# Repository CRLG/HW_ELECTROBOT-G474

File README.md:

# HW_ELECTROBOT-G474
Carte fillepour Nucleo64 G474RE

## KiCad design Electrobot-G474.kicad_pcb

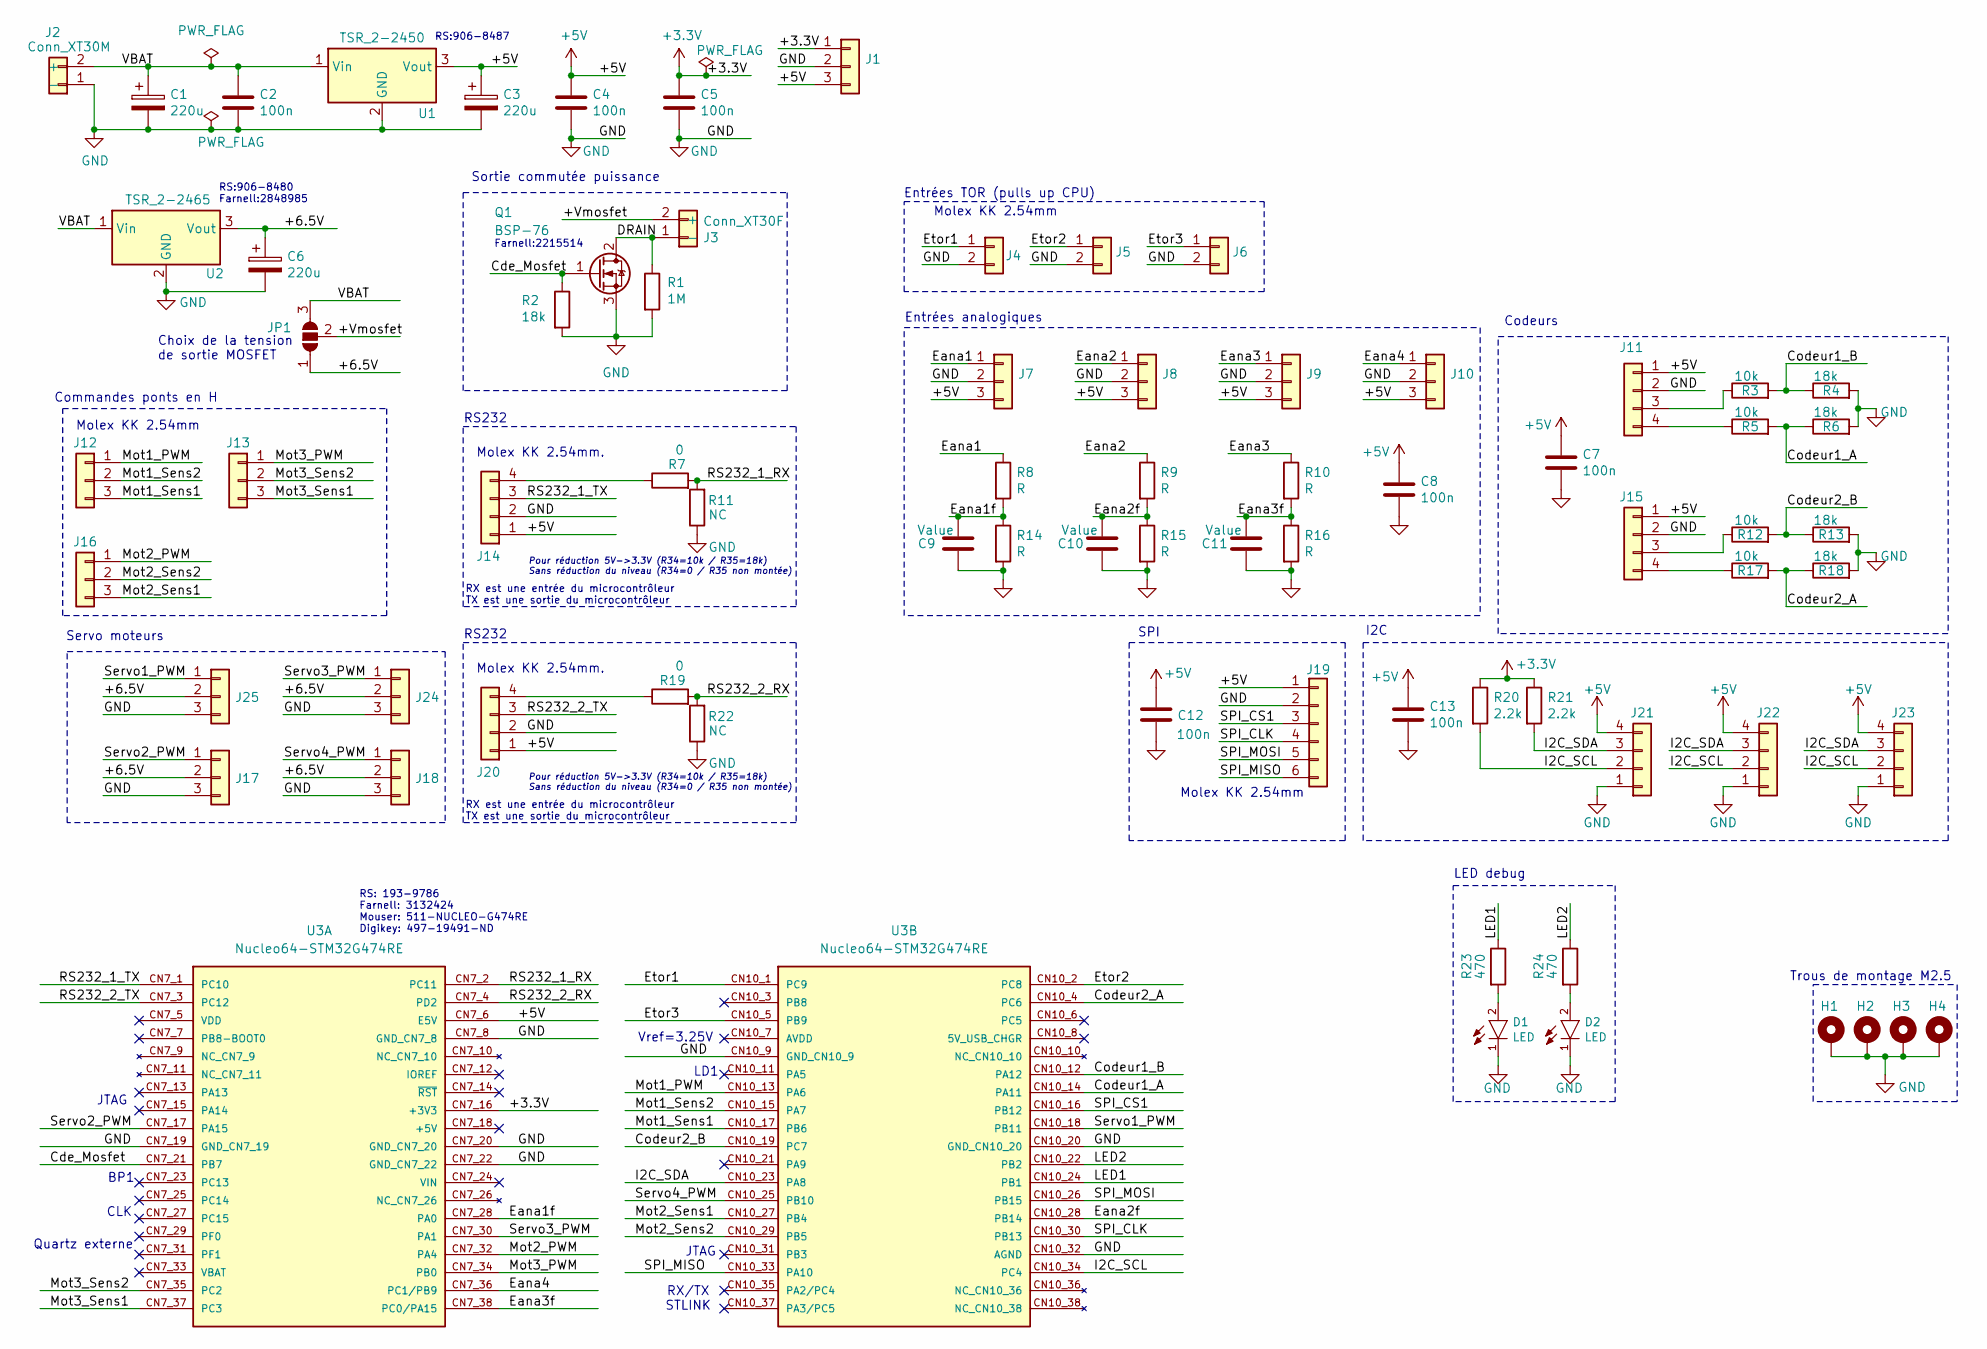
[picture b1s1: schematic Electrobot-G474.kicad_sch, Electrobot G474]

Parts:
C1, C3, C6: 220u; C_Radial_D8.0mm_H11.5mm_P3.50mm
C2, C4, C5, C7, C8, C12, C13: 100n; C_1206_3216Metric
C9, C10, C11: Value; C_1206_3216Metric
D1, D2: LED; LED_1206_3216Metric
H1, H2, H3, H4: MountingHole_Pad; MountingHole_2.7mm_M2.5_Pad
J1, J7, J8, J9, J10: Conn_01x03; Molex_KK-254_AE-6410-03A_1x03_P2.54mm_Vertical
J2: Conn_XT30M; AMASS_XT30UPB-M_1x02_P5.0mm_Vertical
J3: Conn_XT30F; AMASS_XT30UPB-F_1x02_P5.0mm_Vertical
J4, J5, J6: Conn_01x02; Molex_KK-254_AE-6410-02A_1x02_P2.54mm_Vertical
J11, J14, J15, J20, J21, J22, J23: Conn_01x04; Molex_KK-254_AE-6410-04A_1x04_P2.54mm_Vertical
J12, J13, J16: Conn_01x04; Molex_KK-254_AE-6410-03A_1x03_P2.54mm_Vertical
J17, J18, J24, J25: Conn_01x03; Servomotor-3x254
J19: Conn_01x06; Molex_KK-254_AE-6410-06A_1x06_P2.54mm_Vertical
JP1: SolderJumper_3_Open; PinHeader_1x03_P2.54mm_Vertical
Q1: BSP-76; SOT-223-3_TabPin2
R1: 1M; R_1206_3216Metric
R2, R4, R6, R13, R18: 18k; R_1206_3216Metric
R3, R5, R12, R17: 10k; R_1206_3216Metric
R7, R19: 0; R_1206_3216Metric
R8, R9, R10, R14, R15, R16: R; R_1206_3216Metric
R11, R22: NC; R_1206_3216Metric
R20, R21: 2.2k; R_1206_3216Metric
R23, R24: 470; R_1206_3216Metric
U1: TSR_2-2450; Converter_DCDC_TRACO_TSR-2_THT
U2: TSR_2-2465; Converter_DCDC_TRACO_TSR-2_THT
U3: Nucleo64-STM32G474RE; Nucleo64-G474RE_ExtensionShield_Bottom

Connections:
+3.3V: C5.1, J1.1, R20.1, R21.1, U3.CN7_16 (+3V3)
+5V: C3.1, C4.1, C7.1, C8.1, C12.1, C13.1, J1.3, J7.3, J8.3, J9.3, J10.3, J11.1, J14.1, J15.1, J19.1, J20.1, J21.4, J22.4, J23.4, U1.3 (Vout), U3.CN7_6 (E5V)
/+6.5V: C6.1, J17.2, J18.2, J24.2, J25.2, JP1.1 (A), U2.3 (Vout)
/+Vmosfet: J3.2 (+), JP1.2 (C)
/Cde_Mosfet: Q1.1 (G), R2.1, U3.CN7_21 (PB7)
/Codeur1_A: R5.2, R6.1, U3.CN10_14 (PA11)
/Codeur1_B: R3.2, R4.1, U3.CN10_12 (PA12)
/Codeur2_A: R17.2, R18.1, U3.CN10_4 (PC6)
/Codeur2_B: R12.2, R13.1, U3.CN10_19 (PC7)
/DRAIN: J3.1 (-), Q1.2 (D), R1.1
/Eana1: J7.1, R8.1
/Eana1f: C9.2, R8.2, R14.1, U3.CN7_28 (PA0)
/Eana2: J8.1, R9.1
/Eana2f: C10.2, R9.2, R15.1, U3.CN10_28 (PB14)
/Eana3: J9.1, R10.1
/Eana3f: C11.2, R10.2, R16.1, U3.CN7_38 (PC0/PA15)
/Eana4: J10.1, U3.CN7_36 (PC1/PB9)
/Etor1: J4.1, U3.CN10_1 (PC9)
/Etor2: J5.1, U3.CN10_2 (PC8)
/Etor3: J6.1, U3.CN10_5 (PB9)
/I2C_SCL: J21.2, J22.2, J23.2, R20.2, U3.CN10_34 (PC4)
/I2C_SDA: J21.3, J22.3, J23.3, R21.2, U3.CN10_23 (PA8)
/LED1: R23.1, U3.CN10_24 (PB1)
/LED2: R24.1, U3.CN10_22 (PB2)
/Mot1_PWM: J12.1, U3.CN10_13 (PA6)
/Mot1_Sens1: J12.3, U3.CN10_17 (PB6)
/Mot1_Sens2: J12.2, U3.CN10_15 (PA7)
/Mot2_PWM: J16.1, U3.CN7_32 (PA4)
/Mot2_Sens1: J16.3, U3.CN10_27 (PB4)
/Mot2_Sens2: J16.2, U3.CN10_29 (PB5)
/Mot3_PWM: J13.1, U3.CN7_34 (PB0)
/Mot3_Sens1: J13.3, U3.CN7_37 (PC3)
/Mot3_Sens2: J13.2, U3.CN7_35 (PC2)
/RS232_1_RX: R7.2, R11.2, U3.CN7_2 (PC11)
/RS232_1_TX: J14.3, U3.CN7_1 (PC10)
/RS232_2_RX: R19.2, R22.2, U3.CN7_4 (PD2)
/RS232_2_TX: J20.3, U3.CN7_3 (PC12)
/SPI_CLK: J19.4, U3.CN10_30 (PB13)
/SPI_CS1: J19.3, U3.CN10_16 (PB12)
/SPI_MISO: J19.6, U3.CN10_33 (PA10)
/SPI_MOSI: J19.5, U3.CN10_26 (PB15)
/Servo1_PWM: J25.1, U3.CN10_18 (PB11)
/Servo2_PWM: J17.1, U3.CN7_17 (PA15)
/Servo3_PWM: J24.1, U3.CN7_30 (PA1)
/Servo4_PWM: J18.1, U3.CN10_25 (PB10)
/VBAT: C1.1, C2.1, J2.2 (+), JP1.3 (B), U1.1 (Vin), U2.1 (Vin)
GND: C1.2, C2.2, C3.2, C4.2, C5.2, C6.2, C7.2, C8.2, C9.1, C10.1, C11.1, C12.2, C13.2, D1.1 (C), D2.1 (C), H1.1, H2.1, H3.1, H4.1, J1.2, J2.1 (-), J4.2, J5.2, J6.2, J7.2, J8.2, J9.2, J10.2, J11.2, J14.2, J15.2, J17.3, J18.3, J19.2, J20.2, J21.1, J22.1, J23.1, J24.3, J25.3, Q1.3 (S), R1.2, R2.2, R4.2, R6.2, R11.1, R13.2, R14.2, R15.2, R16.2, R18.2, R22.1, U1.2 (GND), U2.2 (GND), U3.CN7_8 (GND_CN7_8), U3.CN7_19 (GND_CN7_19), U3.CN7_20 (GND_CN7_20), U3.CN7_22 (GND_CN7_22), U3.CN10_9 (GND_CN10_9), U3.CN10_20 (GND_CN10_20), U3.CN10_32 (AGND)
unnamed: D1.2 (A), R23.2
unnamed: D2.2 (A), R24.2
unnamed: J11.3, R3.1
unnamed: J11.4, R5.1
unnamed: J14.4, R7.1
unnamed: J15.3, R12.1
unnamed: J15.4, R17.1
unnamed: J20.4, R19.1

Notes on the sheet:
RS232
JTAG
Entrées TOR (pulls up CPU)
Pour réduction 5V->3.3V (R34=10k / R35=18k) Sans réduction du niveau (R34=0 / R35 non montée)
Vref=3.25V
LD1
Farnell:2215514
Trous de montage M2.5
Molex KK 2.54mm
SPI
BP1
RX est une entrée du microcontrôleur TX est une sortie du microcontrôleur
Sortie commutée puissance
Entrées analogiques
RS:906-8487
RX/TX STLINK
Servo moteurs
I2C
Choix de la tension de sortie MOSFET
LED debug
RS:906-8480 Farnell:2848985
Molex KK 2.54mm.
Quartz externe
Commandes ponts en H
RS: 193-9786 Farnell: 3132424 Mouser: 511-NUCLEO-G474RE Digikey: 497-19491-ND
Codeurs
CLK

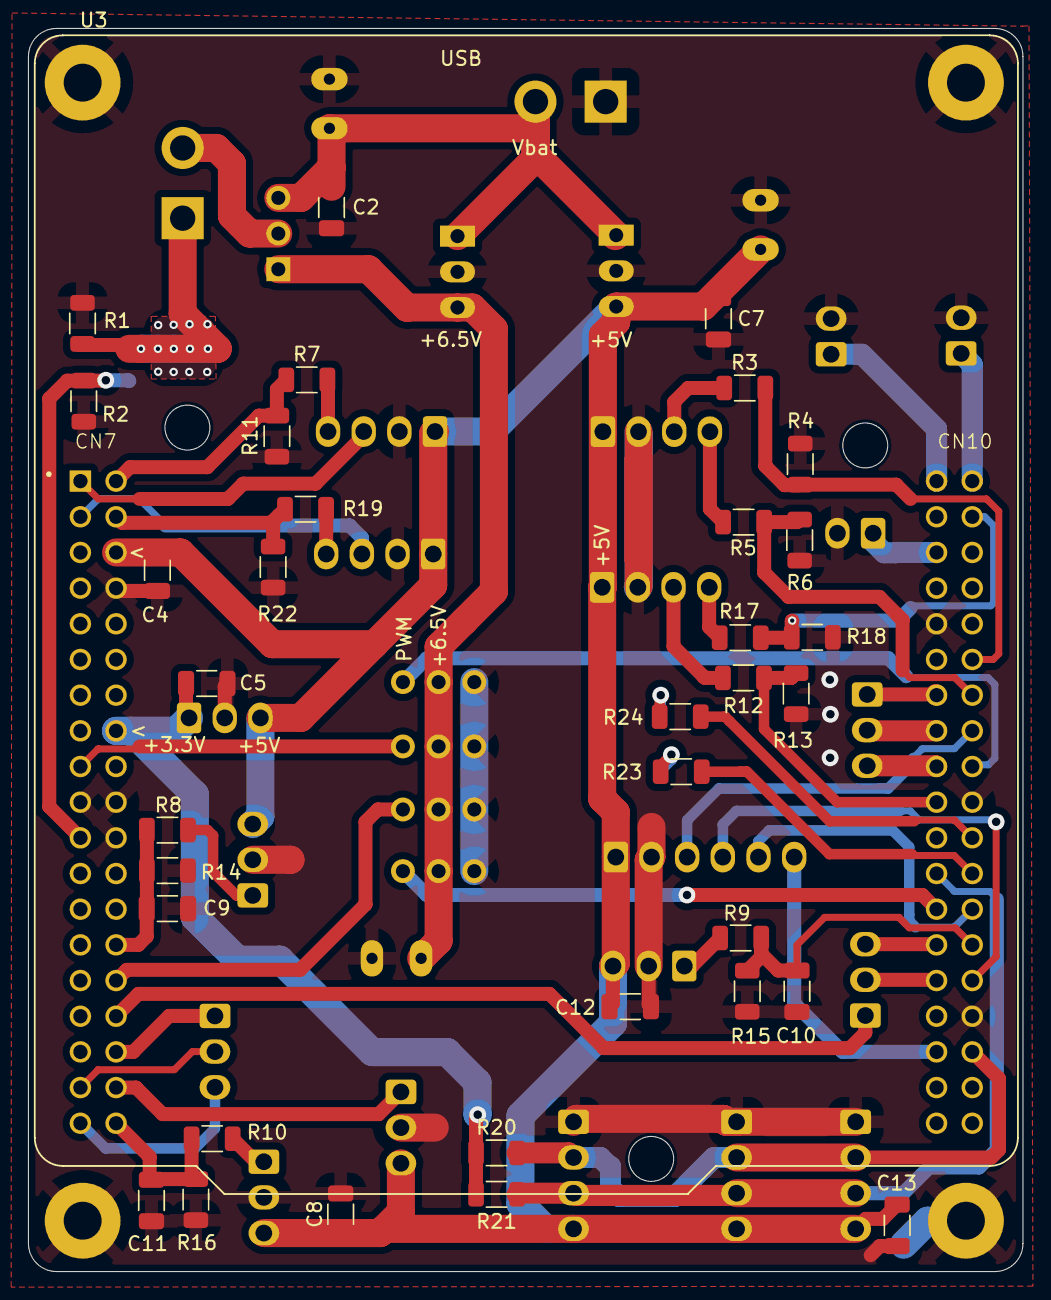
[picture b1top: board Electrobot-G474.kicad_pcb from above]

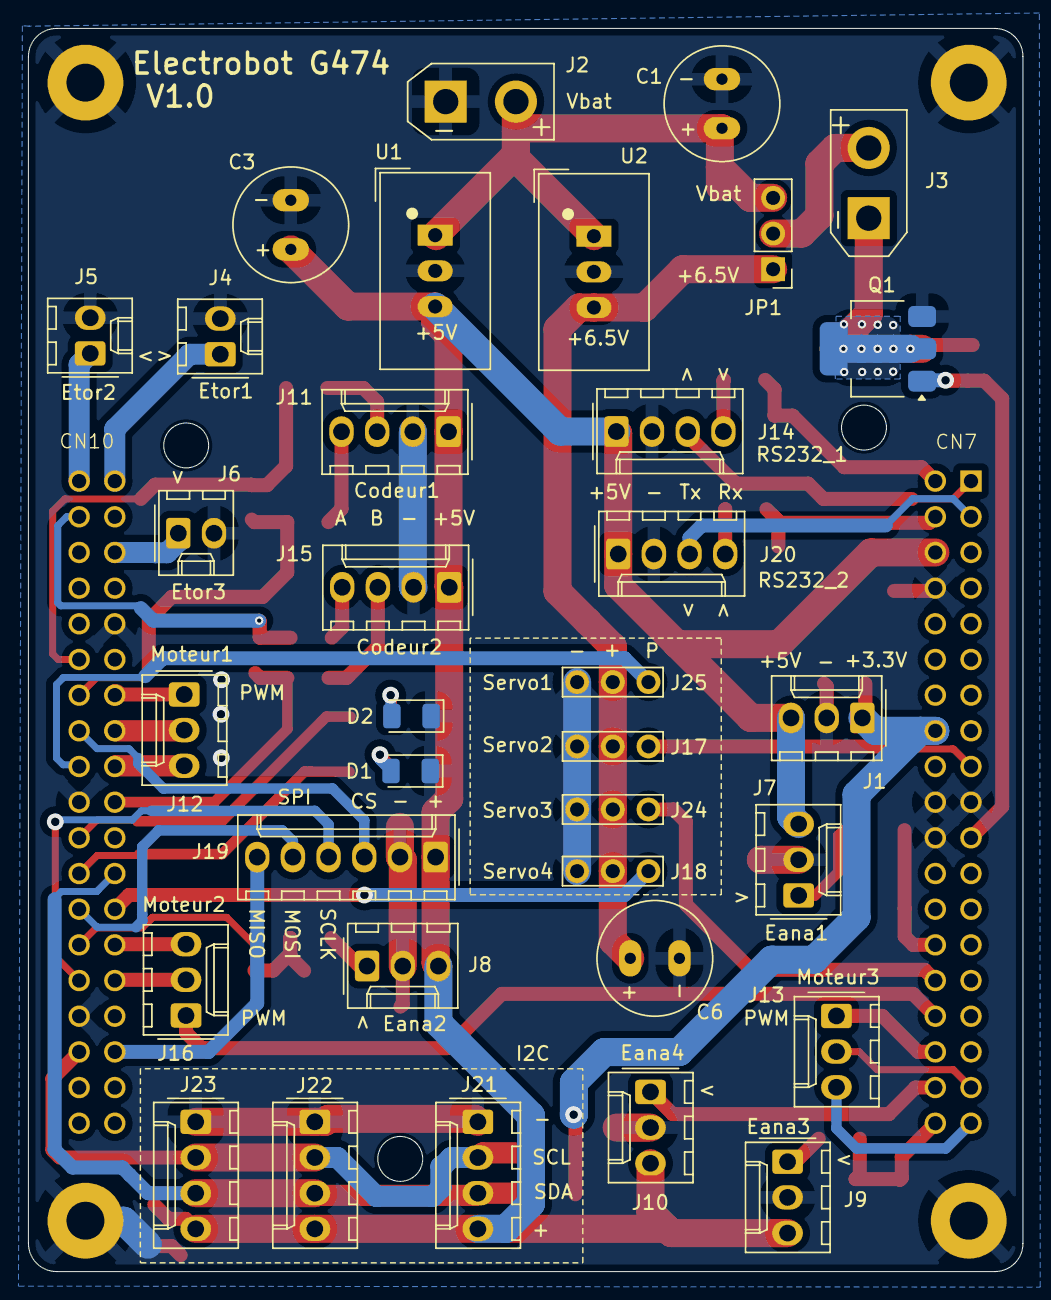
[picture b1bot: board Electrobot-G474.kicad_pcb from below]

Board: 2 copper layers, 70.8 x 88.5 mm, 73 parts (34 on the bottom side), 55 nets.

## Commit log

2025-10-28 Ajout du sous-module KicadLib
2025-10-28 Mise en place de l'ossature du projet (vide)
2025-11-09 Version initiale du projet
2025-12-10 Mise à jour du schéma et routage de la carte
2025-12-20 Correction des annotations du schéma sur la division de tension des RX RS232
